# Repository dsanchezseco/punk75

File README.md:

# punk75
Ortholinear keyboard with 75 keys and all components through hole

Uses an ATmega32A-PU and USB-C.

# BOM list
[BOM list](https://octopart.com/bom-tool/D58T7Rv1)

# Building
[Building guide](https://github.com/dsanchezseco/punk75/blob/master/BUILDING.md)

# Bootloader flashing

Before being able to flash the keymap as regular in QMK using a USB we need to
flash the bootloader first. It is only needed to do this process once if the MCU
does not come already flashed with a bootloader.

Punk75 uses [USBasp](https://www.fischl.de/usbasp/) as bootloader.

To flash USBasp you'll need and *USBasp dongle* or a *pro micro/elite-c*.
Other methods not tested but may work.

To follow the process to flash the bootloader [go here](https://github.com/dsanchezseco/USBaspLoader)
and follow the instructions.

# Keymap flashing
There are two possibilities

## QMK toolbox
TODO

## CLI
TODO

# Cases

## PCB
[PCB case](https://github.com/dsanchezseco/punk75/blob/master/case/PCB/README.md)

## Acrylic
[Acrylic case](https://github.com/dsanchezseco/punk75/blob/master/case/sandwich/README.md)

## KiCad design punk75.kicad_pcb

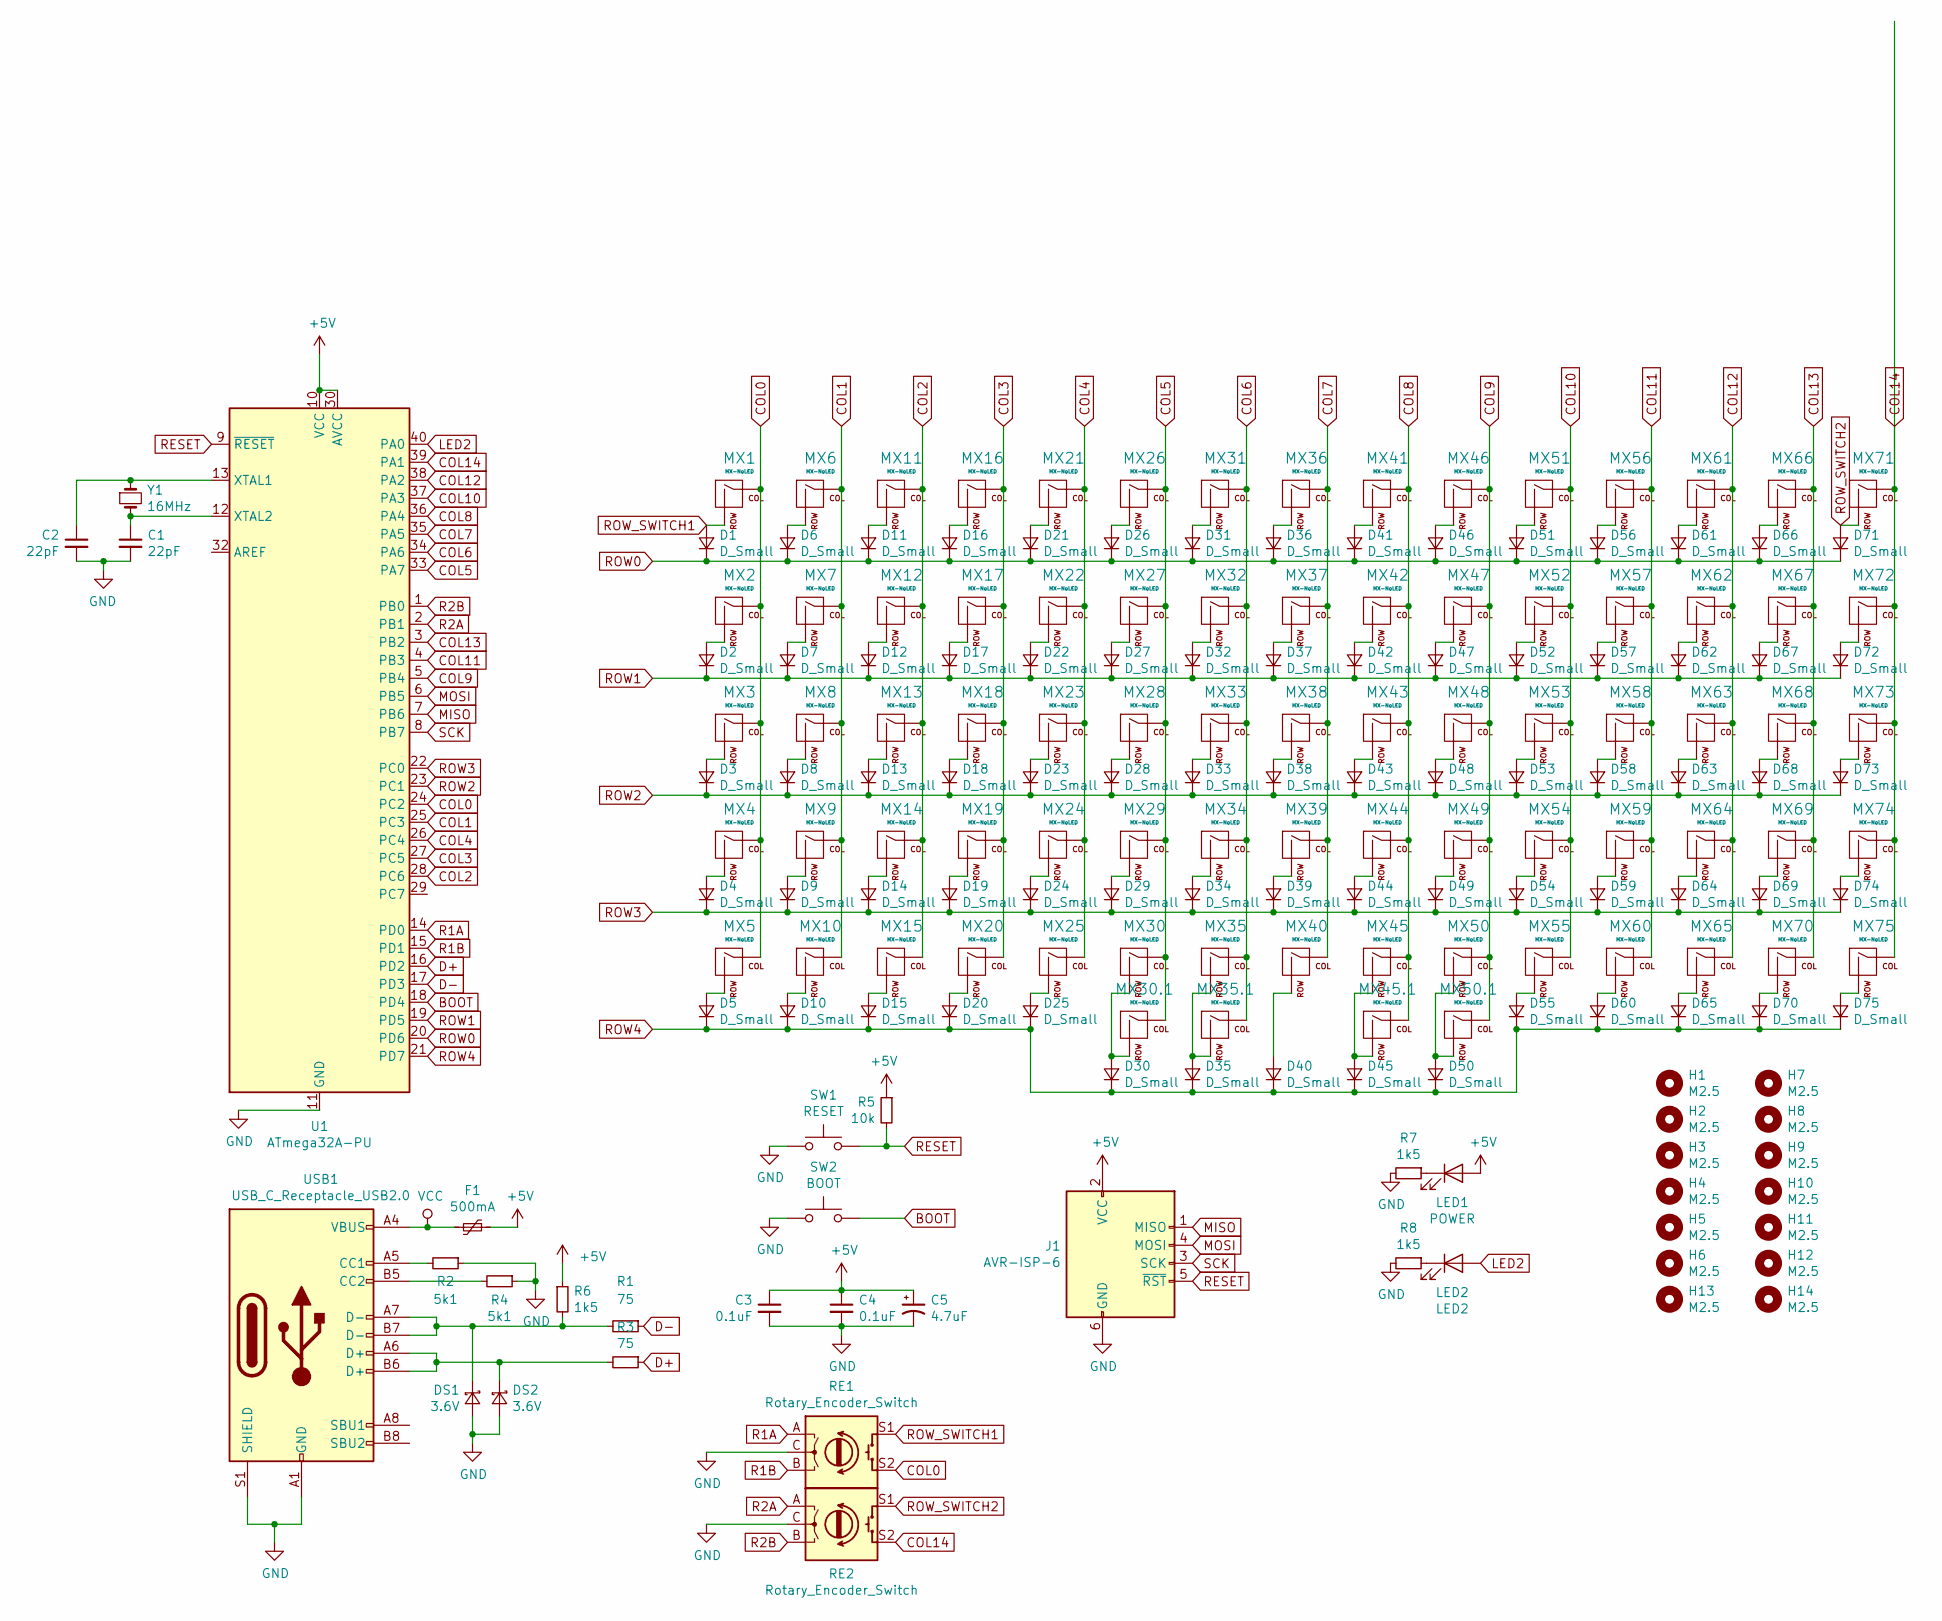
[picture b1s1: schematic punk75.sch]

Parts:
C1, C2: 22pF; C_Disc_D3.0mm_W1.6mm_P2.50mm
C3, C4: 0.1uF; C_Disc_D4.3mm_W1.9mm_P5.00mm
C5: 4.7uF; CP_Radial_D4.0mm_P1.50mm
D1, D2, D3, D4, D5, D6, D7, D8, D9, D10, D11, D12, D13, D14, D15, D16, D17, D18, D19, D20, D21, D22, D23, D24, D25, D26, D27, D28, D29, D30, D31, D32, D33, D34, D35, D36, D37, D38, D39, D40, D41, D42, D43, D44, D45, D46, D47, D48, D49, D50, D51, D52, D53, D54, D55, D56, D57, D58, D59, D60, D61, D62, D63, D64, D65, D66, D67, D68, D69, D70, D71, D72, D73, D74, D75: D_Small; D_DO-35_SOD27_P7.62mm_Horizontal
DS1, DS2: 3.6V; D_DO-35_SOD27_P7.62mm_Horizontal
F1: 500mA; C_Disc_D5.0mm_W2.5mm_P5.00mm
H1, H2, H3, H4, H5, H6, H7, H8, H9, H10, H11, H12, H13, H14: M2.5; MountingHole_2.7mm_M2.5_ISO7380_Pad
J1: AVR-ISP-6; Reset_Pretty-Mask
LED1: POWER; LED_D3.0mm
LED2: LED2; LED_D3.0mm
MX1, MX2, MX3, MX4, MX5, MX6, MX7, MX8, MX9, MX10, MX11, MX12, MX13, MX14, MX15, MX16, MX17, MX18, MX19, MX20, MX21, MX22, MX23, MX24, MX25, MX26, MX27, MX28, MX29, MX30, MX31, MX32, MX33, MX34, MX35, MX36, MX37, MX38, MX39, MX40, MX41, MX42, MX43, MX44, MX45, MX46, MX47, MX48, MX49, MX50, MX51, MX52, MX53, MX54, MX55, MX56, MX57, MX58, MX59, MX60, MX61, MX62, MX63, MX64, MX65, MX66, MX67, MX68, MX69, MX70, MX71, MX72, MX73, MX74, MX75: MX-NoLED; MX-1U-NoLED
MX30.1, MX35.1, MX45.1, MX50.1: MX-NoLED; MX-2U-NoLED
R1, R3: 75; R_Axial_DIN0204_L3.6mm_D1.6mm_P5.08mm_Horizontal
R2, R4: 5k1; R_Axial_DIN0204_L3.6mm_D1.6mm_P5.08mm_Horizontal
R5: 10k; R_Axial_DIN0204_L3.6mm_D1.6mm_P5.08mm_Horizontal
R6, R7, R8: 1k5; R_Axial_DIN0204_L3.6mm_D1.6mm_P5.08mm_Horizontal
RE1, RE2: Rotary_Encoder_Switch; RotaryEncoder_Alps_EC11E-Switch_Vertical_H20mm_CircularMoun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
SW1: RESET; SW_PUSH_6mm
SW2: BOOT; SW_PUSH_6mm
U1: ATmega32A-PU; DIP-40_W15.24mm
USB1: USB_C_Receptacle_USB2.0; USB_C_Receptacle_GCT_USB4085
Y1: 16MHz; Crystal_HC49-4H_Vertical

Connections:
+5V: C3.1, C4.1, C5.1, F1.1, J1.2 (VCC), LED1.2 (A), R5.1, R6.1, U1.10 (VCC), U1.30 (AVCC)
BOOT: SW2.2, U1.18 (PD4)
COL0: MX1.1 (COL), MX2.1 (COL), MX3.1 (COL), MX4.1 (COL), MX5.1 (COL), RE1.S2, U1.24 (PC2)
COL1: MX6.1 (COL), MX7.1 (COL), MX8.1 (COL), MX9.1 (COL), MX10.1 (COL), U1.25 (PC3)
COL2: MX11.1 (COL), MX12.1 (COL), MX13.1 (COL), MX14.1 (COL), MX15.1 (COL), U1.28 (PC6)
COL3: MX16.1 (COL), MX17.1 (COL), MX18.1 (COL), MX19.1 (COL), MX20.1 (COL), U1.27 (PC5)
COL4: MX21.1 (COL), MX22.1 (COL), MX23.1 (COL), MX24.1 (COL), MX25.1 (COL), U1.26 (PC4)
COL6: MX31.1 (COL), MX32.1 (COL), MX33.1 (COL), MX34.1 (COL), MX35.1 (COL), MX35.1.1 (COL), U1.34 (PA6)
COL7: MX36.1 (COL), MX37.1 (COL), MX38.1 (COL), MX39.1 (COL), MX40.1 (COL), U1.35 (PA5)
COL8: MX41.1 (COL), MX42.1 (COL), MX43.1 (COL), MX44.1 (COL), MX45.1 (COL), MX45.1.1 (COL), U1.36 (PA4)
COL9: MX46.1 (COL), MX47.1 (COL), MX48.1 (COL), MX49.1 (COL), MX50.1 (COL), MX50.1.1 (COL), U1.5 (PB4)
COL10: MX51.1 (COL), MX52.1 (COL), MX53.1 (COL), MX54.1 (COL), MX55.1 (COL), U1.37 (PA3)
COL11: MX56.1 (COL), MX57.1 (COL), MX58.1 (COL), MX59.1 (COL), MX60.1 (COL), U1.4 (PB3)
COL12: MX61.1 (COL), MX62.1 (COL), MX63.1 (COL), MX64.1 (COL), MX65.1 (COL), U1.38 (PA2)
COL13: MX66.1 (COL), MX67.1 (COL), MX68.1 (COL), MX69.1 (COL), MX70.1 (COL), U1.3 (PB2)
COL14: MX71.1 (COL), MX72.1 (COL), MX73.1 (COL), MX74.1 (COL), MX75.1 (COL), RE2.S2, U1.39 (PA1)
D+: R3.1, U1.16 (PD2)
D-: R1.1, U1.17 (PD3)
GND: C1.2, C2.2, C3.2, C4.2, C5.2, DS1.2 (A), DS2.2 (A), J1.6 (GND), R2.1, R4.1, R7.2, R8.2, RE1.C, RE2.C, SW1.2, SW2.1, U1.11 (GND), U1.31 (GND), USB1.A1 (GND), USB1.A12 (GND), USB1.B1 (GND), USB1.B12 (GND), USB1.S1 (SHIELD)
LED2: LED2.2 (A), U1.40 (PA0)
MISO: J1.1 (MISO), U1.7 (PB6)
MOSI: J1.4 (MOSI), U1.6 (PB5)
unnamed: C1.1, U1.12 (XTAL2), Y1.2
unnamed: C2.1, U1.13 (XTAL1), Y1.1
unnamed: D2.2 (A), MX2.2 (ROW)
unnamed: D3.2 (A), MX3.2 (ROW)
unnamed: D4.2 (A), MX4.2 (ROW)
unnamed: D5.2 (A), MX5.2 (ROW)
unnamed: D6.2 (A), MX6.2 (ROW)
unnamed: D7.2 (A), MX7.2 (ROW)
unnamed: D8.2 (A), MX8.2 (ROW)
unnamed: D9.2 (A), MX9.2 (ROW)
unnamed: D10.2 (A), MX10.2 (ROW)
unnamed: D11.2 (A), MX11.2 (ROW)
unnamed: D12.2 (A), MX12.2 (ROW)
unnamed: D13.2 (A), MX13.2 (ROW)
unnamed: D14.2 (A), MX14.2 (ROW)
unnamed: D15.2 (A), MX15.2 (ROW)
unnamed: D16.2 (A), MX16.2 (ROW)
unnamed: D17.2 (A), MX17.2 (ROW)
unnamed: D18.2 (A), MX18.2 (ROW)
unnamed: D19.2 (A), MX19.2 (ROW)
unnamed: D20.2 (A), MX20.2 (ROW)
unnamed: D21.2 (A), MX21.2 (ROW)
unnamed: D22.2 (A), MX22.2 (ROW)
unnamed: D23.2 (A), MX23.2 (ROW)
unnamed: D24.2 (A), MX24.2 (ROW)
unnamed: D25.2 (A), MX25.2 (ROW)
unnamed: D26.2 (A), MX26.2 (ROW)
unnamed: D27.2 (A), MX27.2 (ROW)
unnamed: D28.2 (A), MX28.2 (ROW)
unnamed: D29.2 (A), MX29.2 (ROW)
unnamed: D31.2 (A), MX31.2 (ROW)
unnamed: D32.2 (A), MX32.2 (ROW)
unnamed: D33.2 (A), MX33.2 (ROW)
unnamed: D34.2 (A), MX34.2 (ROW)
unnamed: D35.2 (A), MX35.2 (ROW), MX35.1.2 (ROW)
unnamed: D36.2 (A), MX36.2 (ROW)
unnamed: D37.2 (A), MX37.2 (ROW)
unnamed: D38.2 (A), MX38.2 (ROW)
unnamed: D39.2 (A), MX39.2 (ROW)
unnamed: D40.2 (A), MX40.2 (ROW)
unnamed: D41.2 (A), MX41.2 (ROW)
unnamed: D42.2 (A), MX42.2 (ROW)
unnamed: D43.2 (A), MX43.2 (ROW)
unnamed: D44.2 (A), MX44.2 (ROW)
unnamed: D45.2 (A), MX45.2 (ROW), MX45.1.2 (ROW)
unnamed: D46.2 (A), MX46.2 (ROW)
unnamed: D47.2 (A), MX47.2 (ROW)
unnamed: D48.2 (A), MX48.2 (ROW)
unnamed: D49.2 (A), MX49.2 (ROW)
unnamed: D50.2 (A), MX50.2 (ROW), MX50.1.2 (ROW)
unnamed: D51.2 (A), MX51.2 (ROW)
unnamed: D52.2 (A), MX52.2 (ROW)
unnamed: D53.2 (A), MX53.2 (ROW)
unnamed: D54.2 (A), MX54.2 (ROW)
unnamed: D55.2 (A), MX55.2 (ROW)
unnamed: D56.2 (A), MX56.2 (ROW)
unnamed: D57.2 (A), MX57.2 (ROW)
unnamed: D58.2 (A), MX58.2 (ROW)
unnamed: D59.2 (A), MX59.2 (ROW)
unnamed: D60.2 (A), MX60.2 (ROW)
unnamed: D61.2 (A), MX61.2 (ROW)
unnamed: D62.2 (A), MX62.2 (ROW)
unnamed: D63.2 (A), MX63.2 (ROW)
unnamed: D64.2 (A), MX64.2 (ROW)
unnamed: D65.2 (A), MX65.2 (ROW)
unnamed: D66.2 (A), MX66.2 (ROW)
unnamed: D67.2 (A), MX67.2 (ROW)
unnamed: D68.2 (A), MX68.2 (ROW)
unnamed: D69.2 (A), MX69.2 (ROW)
unnamed: D70.2 (A), MX70.2 (ROW)
unnamed: D72.2 (A), MX72.2 (ROW)
unnamed: D73.2 (A), MX73.2 (ROW)
unnamed: D74.2 (A), MX74.2 (ROW)
unnamed: D75.2 (A), MX75.2 (ROW)
unnamed: DS1.1 (K), R1.2, R6.2, USB1.A7 (D-), USB1.B7 (D-)
unnamed: DS2.1 (K), R3.2, USB1.A6 (D+), USB1.B6 (D+)
unnamed: LED1.1 (K), R7.1
unnamed: LED2.1 (K), R8.1
unnamed: R2.2, USB1.A5 (CC1)
unnamed: R4.2, USB1.B5 (CC2)
R1A: RE1.A, U1.14 (PD0)
R1B: RE1.B, U1.15 (PD1)
R2A: RE2.A, U1.2 (PB1)
R2B: RE2.B, U1.1 (PB0)
RESET: J1.5 (~RST), R5.2, SW1.1, U1.9 (~RESET)
ROW0: D1.1 (K), D6.1 (K), D11.1 (K), D16.1 (K), D21.1 (K), D26.1 (K), D31.1 (K), D36.1 (K), D41.1 (K), D46.1 (K), D51.1 (K), D56.1 (K), D61.1 (K), D66.1 (K), D71.1 (K), U1.20 (PD6)
ROW1: D2.1 (K), D7.1 (K), D12.1 (K), D17.1 (K), D22.1 (K), D27.1 (K), D32.1 (K), D37.1 (K), D42.1 (K), D47.1 (K), D52.1 (K), D57.1 (K), D62.1 (K), D67.1 (K), D72.1 (K), U1.19 (PD5)
ROW2: D3.1 (K), D8.1 (K), D13.1 (K), D18.1 (K), D23.1 (K), D28.1 (K), D33.1 (K), D38.1 (K), D43.1 (K), D48.1 (K), D53.1 (K), D58.1 (K), D63.1 (K), D68.1 (K), D73.1 (K), U1.23 (PC1)
ROW3: D4.1 (K), D9.1 (K), D14.1 (K), D19.1 (K), D24.1 (K), D29.1 (K), D34.1 (K), D39.1 (K), D44.1 (K), D49.1 (K), D54.1 (K), D59.1 (K), D64.1 (K), D69.1 (K), D74.1 (K), U1.22 (PC0)
ROW4: D5.1 (K), D10.1 (K), D15.1 (K), D20.1 (K), D25.1 (K), D30.1 (K), D35.1 (K), D40.1 (K), D45.1 (K), D50.1 (K), D55.1 (K), D60.1 (K), D65.1 (K), D70.1 (K), D75.1 (K), U1.21 (PD7)
ROW_SWITCH1: D1.2 (A), MX1.2 (ROW), RE1.S1
ROW_SWITCH2: D71.2 (A), MX71.2 (ROW), RE2.S1
SCK: J1.3 (SCK), U1.8 (PB7)
VCC: F1.2, USB1.A4 (VBUS), USB1.A9 (VBUS), USB1.B4 (VBUS), USB1.B9 (VBUS)

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
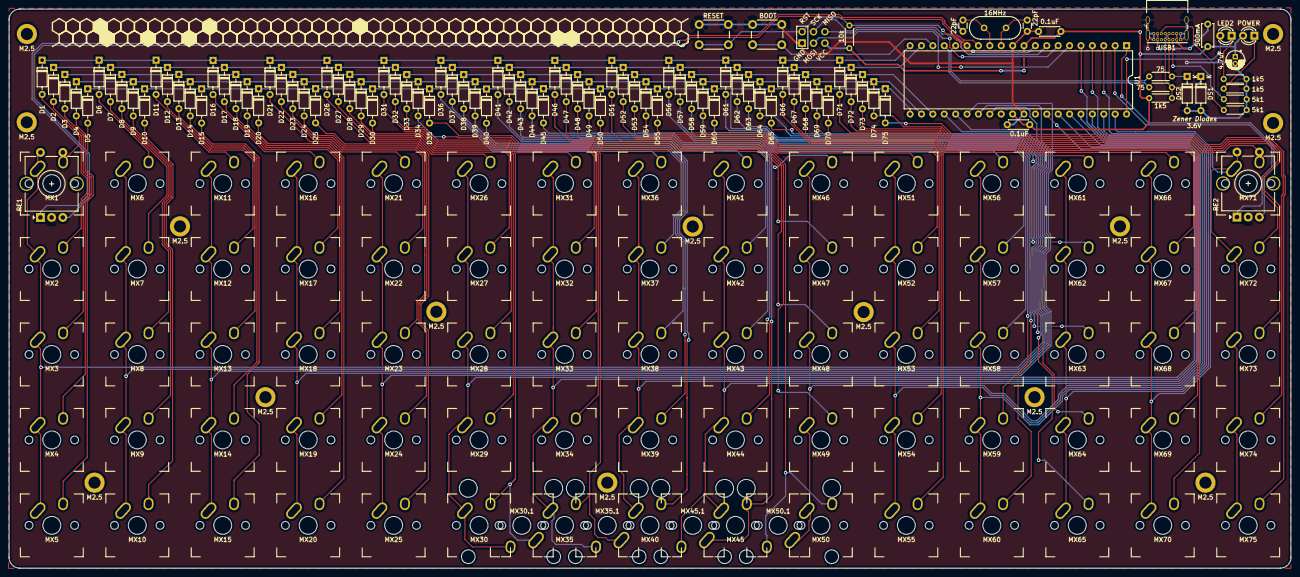
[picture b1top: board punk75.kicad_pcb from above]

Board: 2 copper layers, 285.8 x 124.6 mm, 194 parts (0 on the bottom side), 118 nets.

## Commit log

2020-05-10 added submodules
2020-05-10 pcb files
2020-05-10 added extra switches to allow 2u in bottom row
2020-05-11 added BOM file with components
2020-05-11 added supplier for usb-c sockets
2020-05-11 changed usb tracks using differential pair
2020-05-11 added extra decoration
2020-05-11 added BOM list to readme and images
2020-05-12 updated images and added wiring diagram in pdf
2020-05-14 changed MX-1U-NoLED footprint to be one oval one instead of two overlaped
2020-05-14 changed switch footprint lib back to hybrid alps-mx
2020-05-14 adjusted footprint to support millmax
2020-05-15 updated README with start of flashing instructions
2020-05-16 removed MX_Alps lib to be replaced with my fork
2020-05-16 my MX_Alps footprint lib
2020-05-17 changed switches lib to my modded branch
2020-05-17 changed footprints to my modded MX-Alps hybrids
2020-05-17 updated images and pdf
2020-05-17 added configurable led and rewired all colums to new ports
2020-05-18 added 2 rotary encoders and changed some traces to use them
2020-05-19 fixed silkS of LED2 resistor
2020-05-19 changed filled zones to have thermal reliefs for easier soldering
2020-05-20 added 3d model for usbc connector
2020-05-20 removed old custom footprints
2020-05-20 moved usb-c closer to edge
    now it protudes a bit for easier usage
    added missing 3d models for dip socket and ISP header
2020-05-20 added 3dmodels for rotary encoder and cherry mx
2020-05-20 added 3d switches to all switches(except one rotary encoder)
2020-05-20 added two more mounting holes and moved other two
2020-05-20 updated switches footprint lib
2020-05-20 moved images, 3dmodel of switches and step file
2020-05-20 updated lib
2020-05-20 organized in folders
2020-05-20 step with pcb only
2020-05-20 added 3d stabilizers
2020-05-20 updated step with stabs
2020-05-20 updated pcb with stabs
2020-05-20 fixed the 3dmodels
2020-05-20 3dmodel for usb fixed
2020-05-20 updated images
2020-05-20 added gerber files
2020-05-20 gerber zip
2020-05-21 fixes git submodules
2020-05-21 removed libs to be added as modules
2020-05-21 added libs back as modules
2020-05-21 started Makefile for easier generation of output files
2020-05-21 rerouted crystal zone with better shielding
2020-05-21 makefile creates step model of pcb w/o any component
2020-05-21 moved holes(again...)
2020-05-21 updated 3dmodels
2020-05-21 fixed keep-out zone in crystal surroundings
2020-05-21 adjusted
2020-06-10 case files and render
2020-06-10 moved case generated to case folder
2020-06-10 added the renamed folder
2020-06-10 moved igs
2020-06-10 added README for HI-PRO case
2020-06-10 changed link to README
2020-06-10 fix readme
2020-06-16 new plate and bottom with holes
2020-06-16 added bottom and plate(WIP) pcb files
2020-06-16 plate now have the holes(WIP round corners)
2020-06-16 inner layer pcb
2020-06-16 fixed plate dimensions and rounder corners
2020-06-16 pcb plate
2020-06-17 bottom pcb plate graphics and photos
2020-06-17 same for plate
2020-06-17 images for inner layer
2020-06-17 fixed silk of pcb
2020-06-18 bottom silk lines wider
2020-06-18 fixed plate upper lip to be >3mm
2020-06-18 plate change made in the pcb
2020-06-22 fixed plate and inner holes
2020-06-22 fixed bottom as well removing cuts under footprints
2020-07-15 readme for PCB case
2020-07-15 files of pcb case
2020-07-15 files for pcb case
2020-07-15 encoder note
2020-07-15 added build guide, needs photos!
2020-07-19 added half-shield acrylic dxf for low-pro cases
2020-11-12 start of EOTW case version
2020-11-14 added bottom plate for the EOTW version
    Added bottom plate for the "easy on the wallet" version of the case.
    This plate if smaller intended to use standoffs connected to the pcb instead of being
    a full case
2020-11-14 added eotw plate
    also fixed straight cuts being two different lines instead of one
2020-11-15 linked case gerber files to eotw case folder
2021-01-27 added image of completed keyboard with new keycaps and full case
2021-01-27 added back image and renamed images to change links
2021-02-10 Added Simple High Profile 3D Printed Case
2021-02-10 Added assembly instructions for 3d printed case designs
2021-02-10 Fix formatting issues with GH markdown
2021-02-10 Added note about 3d printed cases using the half shield dxf
